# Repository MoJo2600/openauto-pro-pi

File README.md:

# Automotive power hat for OpenAuto

This hat is designed to work together with OpenAuto Pro and deliver some functionality which makes integrating OpenAuto into your car easier.

## Work in progress - a word of warning

I'm not an electronics professional and this board is currently work in progress. If somebody is willing to do a indepth review with me I would be very glad. Reach out to me on twitter [@MoJo2600](https://twitter.com/MoJo2600).

## Features

* Integrated 5A Power Supply
* Wide range power input (+7.5V to +40V)
* On-/Off circuit with ignition sensing
* 2 Digital inputs for e.g. reverse signal
* I2S sound
* RTC clock
* CSI to HDMI adapters to connect a display and camera
  * I2C bus availabe on the display connector for a light sensor
* Designed to fit exactly onto a [Geekworm x825](https://wiki.geekworm.com/index.php/X825) SSD V1 (Not tested with V2 but should fit)

## Connections
the following pins are used on the pi.

|Connection     | Pin |
|---------------|-----|
|I2C            |BCM23|
|I2C            |BCM24|
|REVERSE        |BCM8 |
|LIGHT          |BCM25|
|PI UP          |BCM23|
|SHUTDOWN       |BCM24|
|I2S DAC MUTE   |BCM16|
|I2S DAC BITCLK |BCM18|
|I2S DAC LRCLK  |BCM19|
|I2S DAC DATAIN |BCM21|

## OpenAuto Pro Setup

Set up the device before you add the header to the raspberry pi. The device will constantly reboot if the Start / Stop script is not installed. An alternative is to bridge the 3.3V pin from the raspberry pi to BCM23.

### Start / Stop script

Copy `scripts/startstop.sh` to the openauto device.

`sudo bash startstop.sh`

### I2C Real Time Clock

Make sure the battery has contact to the pad on the minus size. Mine had not and I added a little bit of solder to the pad to make contact.

```
# select pcf85063
```

### Rearview camera script

This script will open raspivid and show the picture of the rear camera.

Copy all files to the raspberry pi and start the setup

`./setup.sh`

### Brightness control script

My brightness script utilizes the TSL2561 ambient light sensor. The script implements a recommendation from analog devices
https://www.analog.com/en/design-notes/a-simple-implementation-of-lcd-brightness-control-using-the-max44009-ambientlight-sensor.html

Copy all files to the raspberry pi and start the setup

`./setup.sh`

### Audio output

The current audio circuit is not really usable. The output is very noisy und the signal is too low to usw it effectively. If you want to try i t you can use the following settings.

Add the overlays to `/boot/config.txt`

```
dtoverlay=hifiberry-dac
dtoverlay=i2s-mmap
```

After a reboot the sound should be working. Expect a line level output. If the volume is set to high, there will be clipping.

## Fixes for Issues

### Bluetooth Dongle BCM20702A1 not working

I had to install the bluetooth firmware for my broadcom bluetooth dongle from this repository https://github.com/winterheart/broadcom-bt-firmware.

The error in dmesg was:

```
bluetooth hci1: Direct firmware load for brcm/BCM20702A1-0a5c-21e8 failed with error -2
Bluetooth: hci1: BCM: Patch brcm/BCM20702A1-0a5c-21e8 not found
```

The installation was easy:

```
wget https://github.com/winterheart/broadcom-bt-firmware/raw/master/brcm/BCM20702A1-0a5c-21e8.hcd
sudo cp *.hcd /lib/firmware/brcm/
```

## History

Here is a picture of prototype V1 with a Mouseberry power supply.

## Disclaimer

Due to the fact we are not providing a product in the legal sense, we are also not providing any warranty in any aspect.

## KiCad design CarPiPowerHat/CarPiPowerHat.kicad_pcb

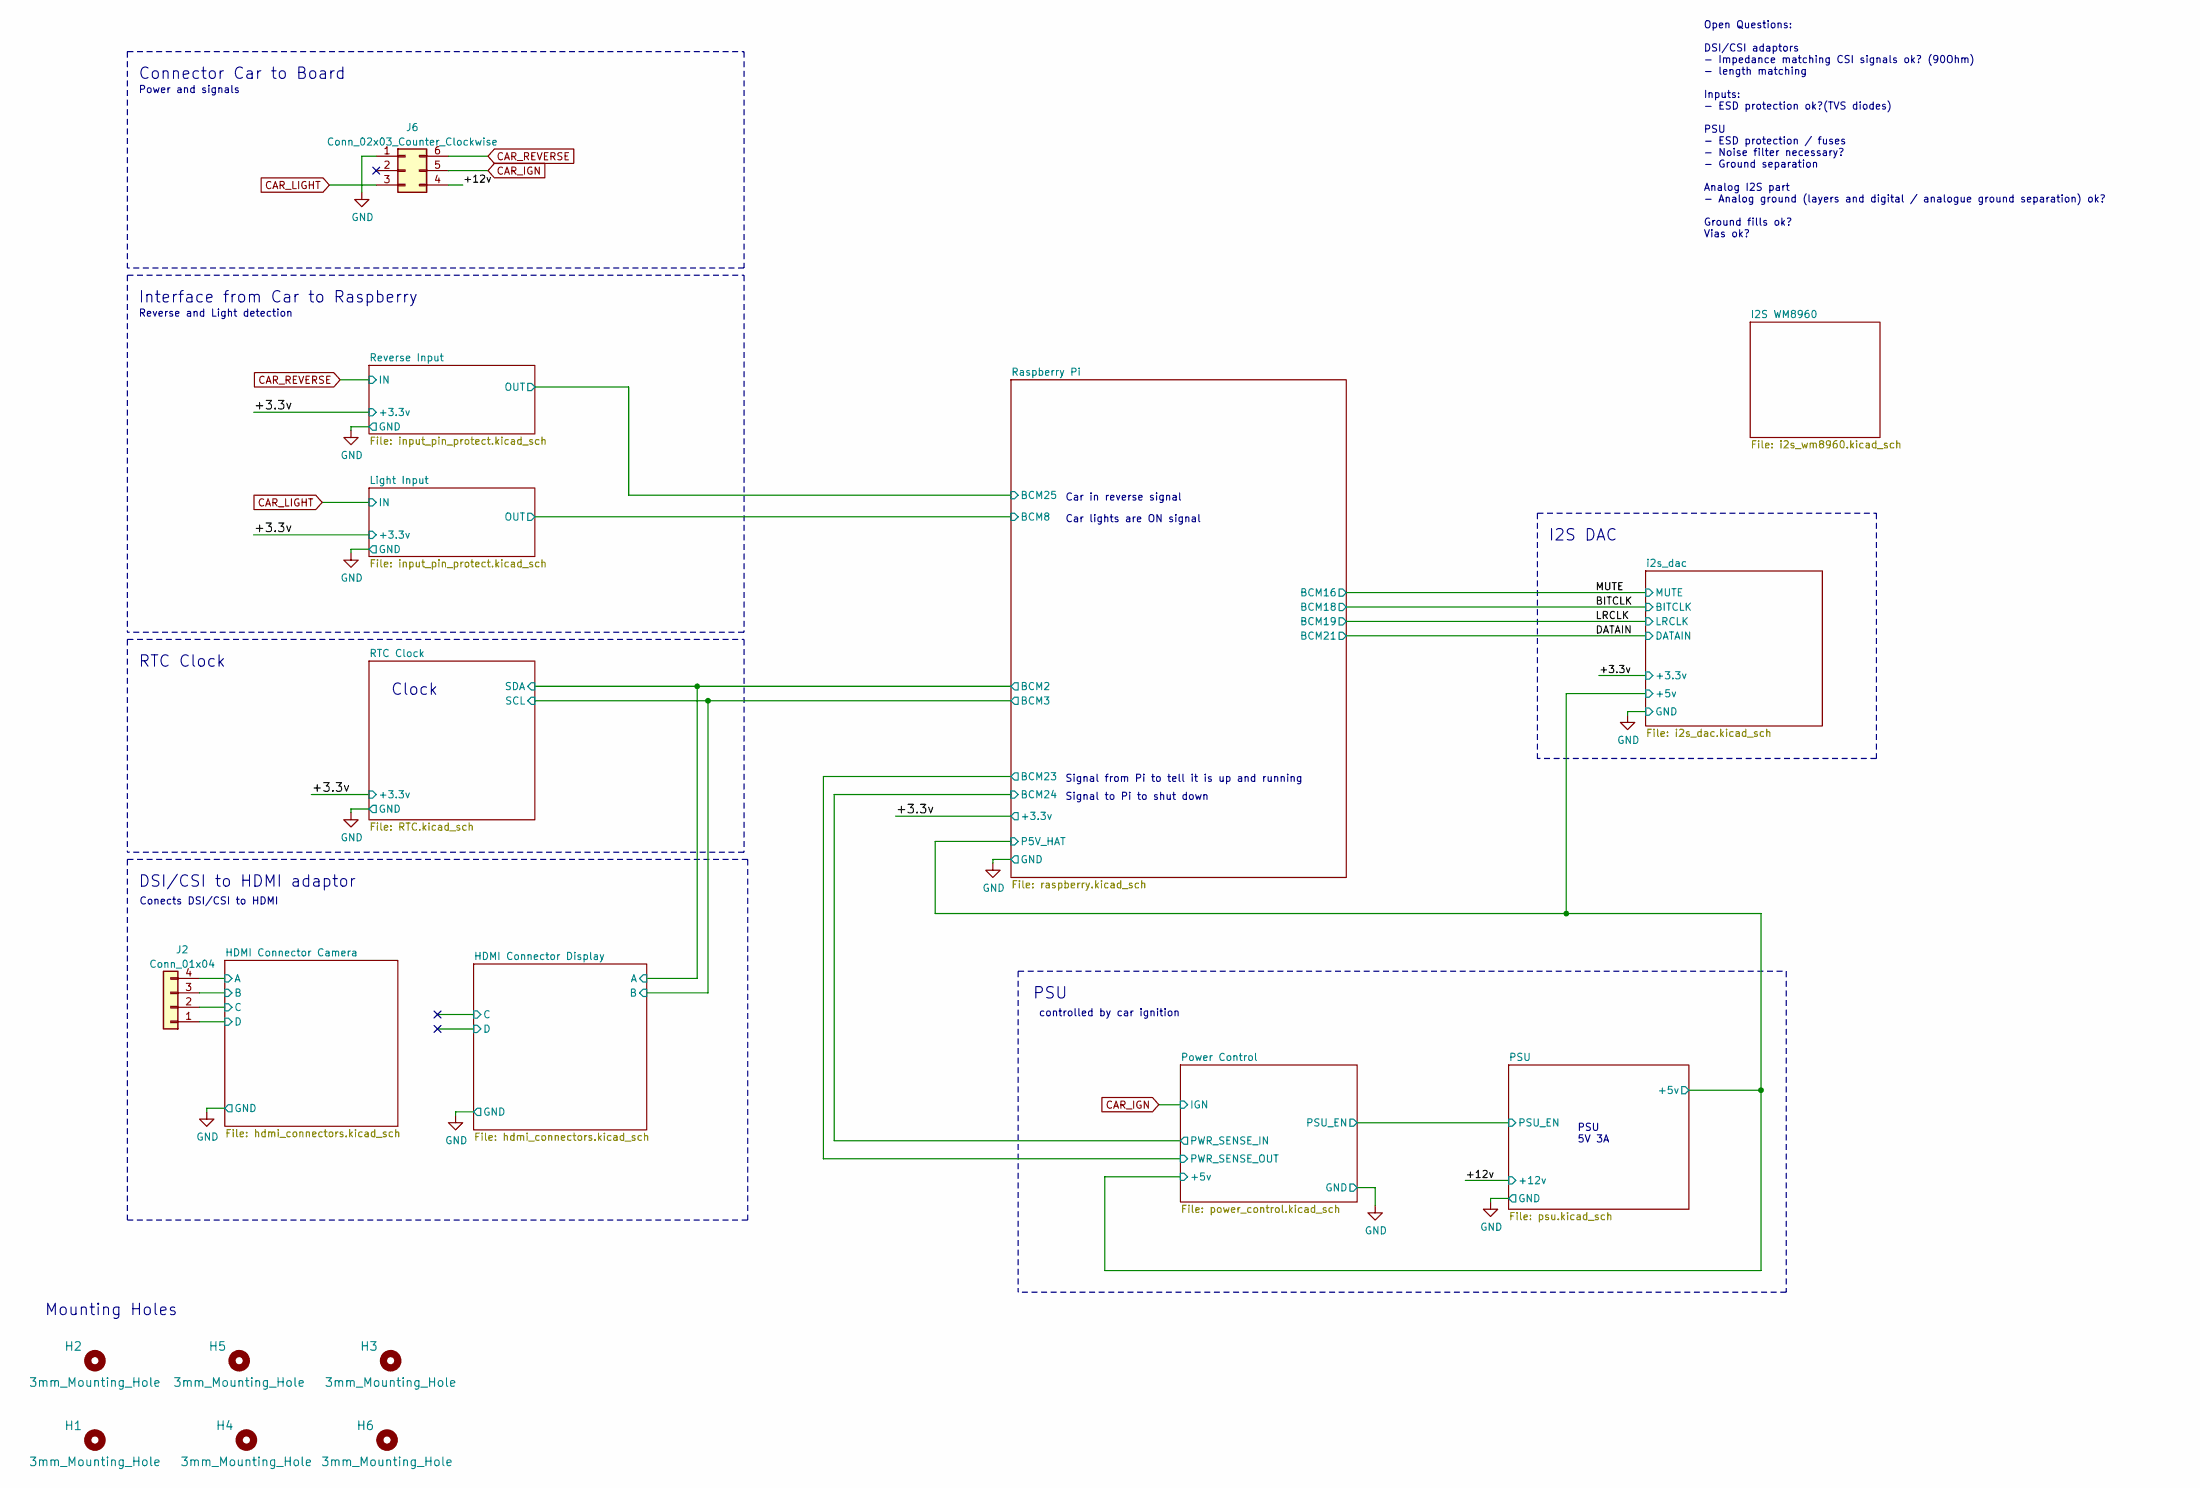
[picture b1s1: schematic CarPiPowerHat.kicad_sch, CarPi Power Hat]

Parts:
H1, H2, H3, H4, H5, H6: 3mm_Mounting_Hole; MountingHole_2.7mm_M2.5
J2: Conn_01x04; PinHeader_1x04_P2.00mm_Vertical
J6: Conn_02x03_Counter_Clockwise; Molex_Mini-Fit_Jr_5569-06A2_2x03_P4.20mm_Horizontal; MouserNr 538-50-36-1798

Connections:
/+12v: J6.4; also elsewhere on the board
/HDMI Connector Camera/A: J2.4; also elsewhere on the board
/HDMI Connector Camera/B: J2.3; also elsewhere on the board
/HDMI Connector Camera/C: J2.2; also elsewhere on the board
/HDMI Connector Camera/D: J2.1; also elsewhere on the board
CAR_IGN: J6.5; also elsewhere on the board
CAR_LIGHT: J6.3; also elsewhere on the board
CAR_REVERSE: J6.6; also elsewhere on the board
GND: J6.1; also elsewhere on the board

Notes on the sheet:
Open Questions: DSI/CSI adaptors - Impedance matching CSI signals ok? (90Ohm) - length matching Inputs: - ESD protection ok?(TVS diodes) PSU - ESD protection / fuses - Noise filter necessary? - Ground separation Analog I2S part - Analog ground (layers and digital / analogue ground separation) ok? G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
PSU 5V 3A
Mounting Holes
Power and signals
PSU
I2S DAC
RTC Clock
controlled by car ignition
Clock
Signal to Pi to shut down
Signal from Pi to tell it is up and running
Car lights are ON signal
Connector Car to Board
DSI/CSI to HDMI adaptor
Reverse and Light detection
Conects DSI/CSI to HDMI
Car in reverse signal
Interface from Car to Raspberry

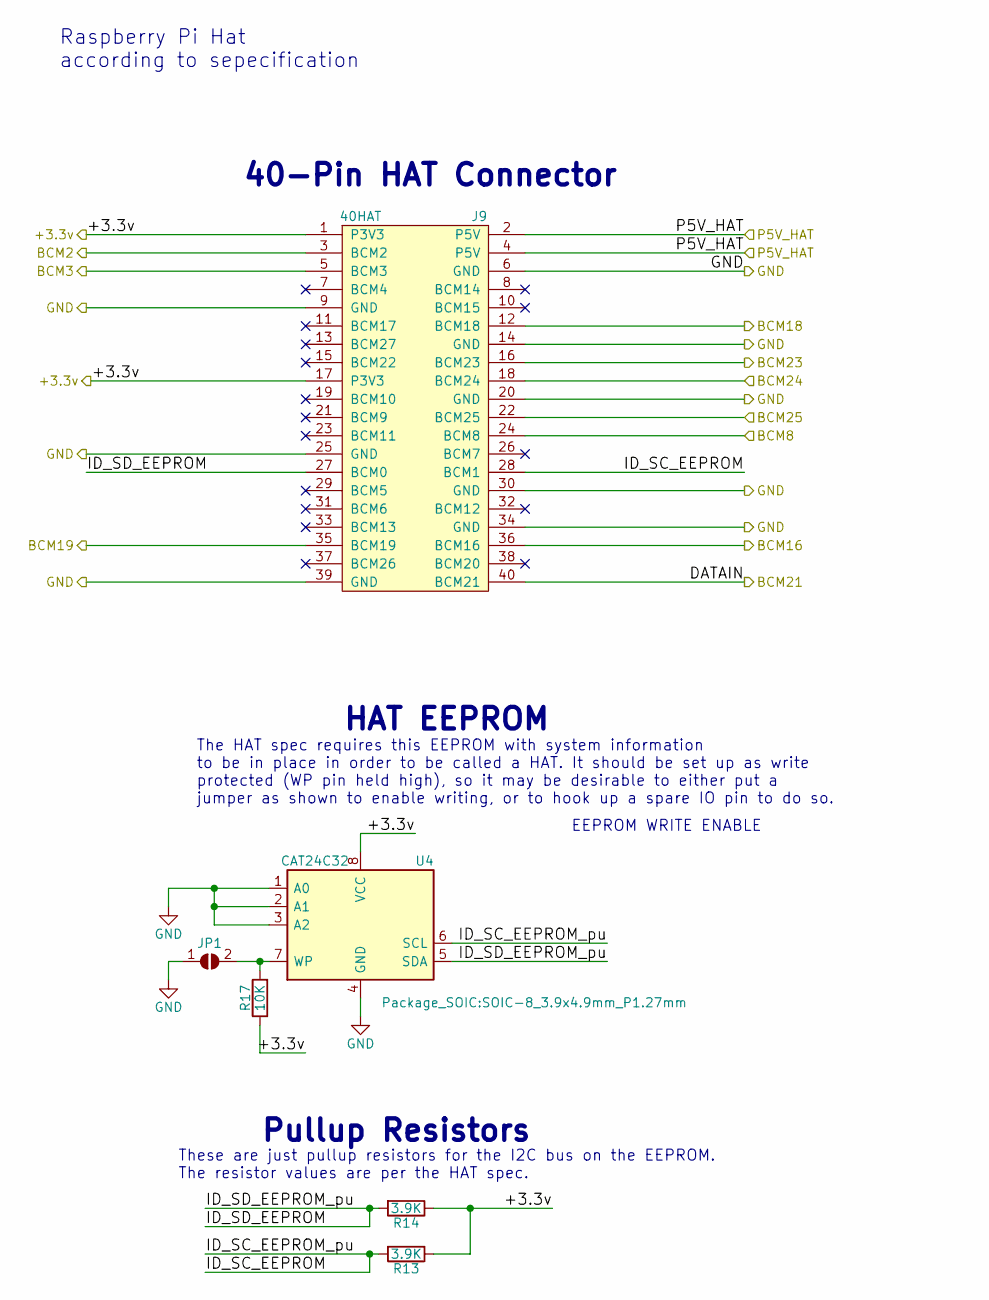
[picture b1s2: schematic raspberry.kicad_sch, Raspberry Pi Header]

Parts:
J9: 40HAT; PinSocket_2x20_P2.54mm_Vertical
JP1: SolderJumper_2_Open; SolderJumper-2_P1.3mm_Open_RoundedPad1.0x1.5mm
R13, R14: 3.9K; R_0603_1608Metric; LCSC C23018
R17: 10K; R_0603_1608Metric; LCSC C25804
U4: CAT24C32; SOIC-8_3.9x4.9mm_P1.27mm; LCSC C81193

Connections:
/+3.3v: J9.1 (P3V3), J9.17 (P3V3), R13.1, R14.1, R17.1, U4.8 (VCC); also elsewhere on the board
/BITCLK: J9.12 (BCM18); also elsewhere on the board
/DATAIN: J9.40 (BCM21); also elsewhere on the board
/LRCLK: J9.35 (BCM19); also elsewhere on the board
/Light Input/OUT: J9.24 (BCM8); also elsewhere on the board
/MUTE: J9.36 (BCM16); also elsewhere on the board
/Power Control/PWR_SENSE_IN: J9.18 (BCM24); also elsewhere on the board
/RTC Clock/SCL: J9.5 (BCM3); also elsewhere on the board
/RTC Clock/SDA: J9.3 (BCM2); also elsewhere on the board
/Raspberry Pi/BCM25: J9.22 (BCM25); also elsewhere on the board
/Raspberry Pi/ID_SC_EEPROM: J9.28 (BCM1), R13.2, U4.6 (SCL)
/Raspberry Pi/ID_SD_EEPROM: J9.27 (BCM0), R14.2, U4.5 (SDA)
/Raspberry Pi/P5V_HAT: J9.2 (P5V), J9.4 (P5V); also elsewhere on the board
GND: J9.6 (GND), J9.9 (GND), J9.14 (GND), J9.20 (GND), J9.25 (GND), J9.30 (GND), J9.34 (GND), J9.39 (GND), JP1.1 (A), U4.1 (A0), U4.2 (A1), U4.3 (A2), U4.4 (GND); also elsewhere on the board
unnamed: JP1.2 (B), R17.2, U4.7 (WP)
PWR_SENSE_OUT: J9.16 (BCM23); also elsewhere on the board

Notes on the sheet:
EEPROM WRITE ENABLE
Pullup Resistors
40-Pin HAT Connector
HAT EEPROM
The HAT spec requires this EEPROM with system information to be in place in order to be called a HAT. It should be set up as write protected (WP pin held high), so it may be desirable to either put a jumper as shown to enable writing, or to hook up a spare IO pin to do so.
Raspberry Pi Hat according to sepecification
These are just pullup resistors for the I2C bus on the EEPROM. The resistor values are per the HAT spec.

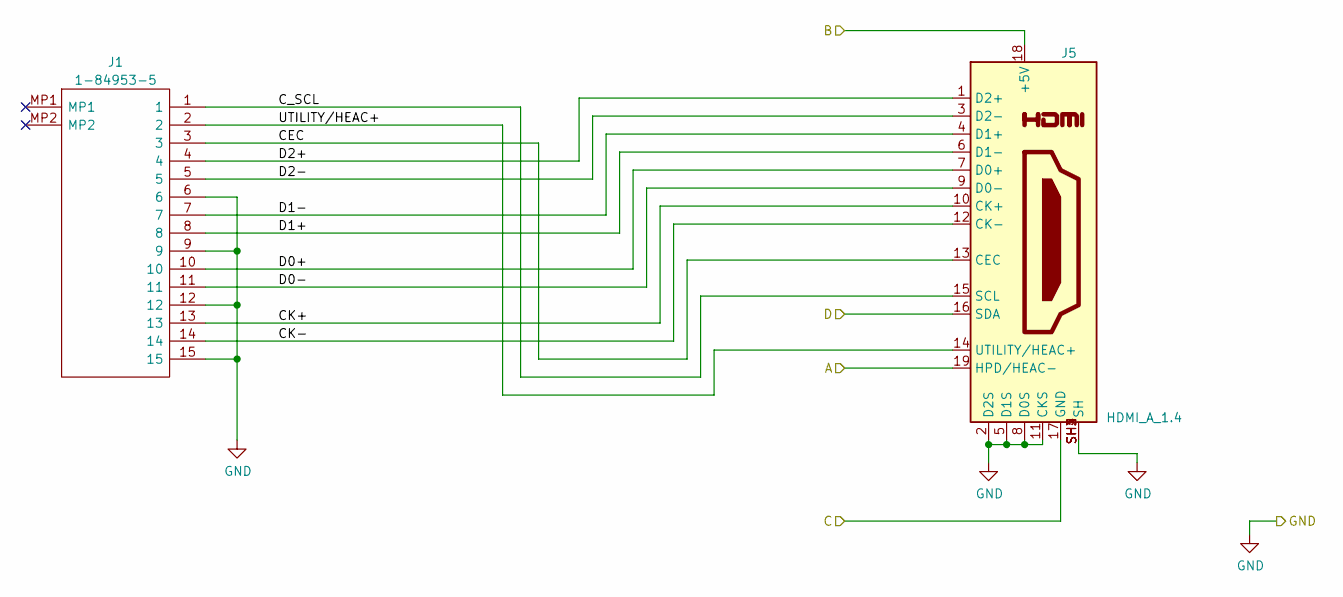
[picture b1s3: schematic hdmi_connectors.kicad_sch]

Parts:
J1: 1-84953-5; 1849535; Manufacturer_Part_Number 1-84953-5; Mouser Part Number 571-1-84953-5
J5: HDMI_A_1.4; EDAC 690-019-298-412; Part Description HDMI Connector, Right Angle, 19 Contact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

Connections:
/HDMI Connector Display/C: J5.17 (GND)
/HDMI Connector Display/CEC: J1.3, J5.13 (CEC)
/HDMI Connector Display/CK+: J1.13, J5.10 (CK+)
/HDMI Connector Display/CK-: J1.14, J5.12 (CK-)
/HDMI Connector Display/C_SCL: J1.1, J5.15 (SCL)
/HDMI Connector Display/D: J5.16 (SDA)
/HDMI Connector Display/D0+: J1.10, J5.7 (D0+)
/HDMI Connector Display/D0-: J1.11, J5.9 (D0-)
/HDMI Connector Display/D1+: J1.8, J5.6 (D1-)
/HDMI Connector Display/D1-: J1.7, J5.4 (D1+)
/HDMI Connector Display/D2+: J1.4, J5.1 (D2+)
/HDMI Connector Display/D2-: J1.5, J5.3 (D2-)
/HDMI Connector Display/UTILITY/HEAC+: J1.2, J5.14 (UTILITY/HEAC+)
/RTC Clock/SCL: J5.18 (+5V); also elsewhere on the board
/RTC Clock/SDA: J5.19 (HPD/HEAC-); also elsewhere on the board
GND: J1.6, J1.9, J1.12, J1.15, J5.2 (D2S), J5.5 (D1S), J5.8 (D0S), J5.11 (CKS), J5.SH1 (SH), J5.SH2 (SH), J5.SH3 (SH), J5.SH4 (SH); also elsewhere on the board

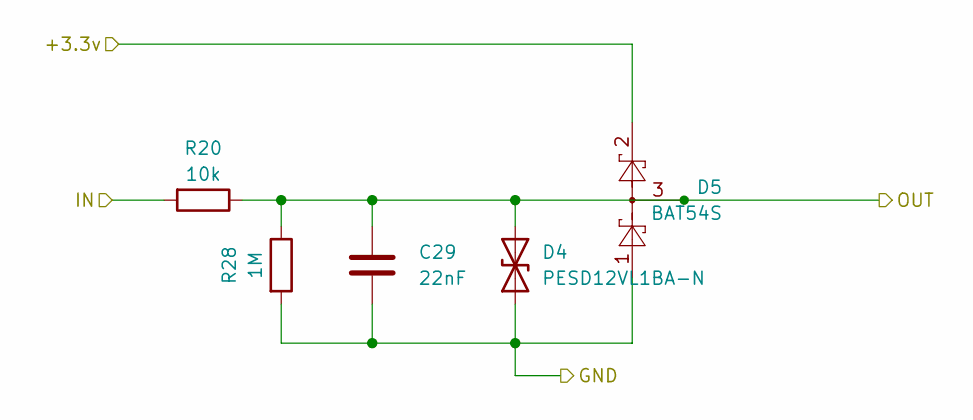
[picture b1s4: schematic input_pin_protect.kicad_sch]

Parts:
C29: 22nF; C_0805_2012Metric; LCSC C1729
D4: PESD12VL1BA-N; D_SOD-323; LCSC C314261
D5: BAT54S; SOT-23; LCSC C408389
R20: 10k; R_0805_2012Metric_Pad1.20x1.40mm_HandSolder; LCSC C17414
R28: 1M; R_0805_2012Metric_Pad1.20x1.40mm_HandSolder; LCSC C17514

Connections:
/+3.3v: D5.2; also elsewhere on the board
/Raspberry Pi/BCM25: C29.1, D4.2 (A2), D5.3, R20.1, R28.1; also elsewhere on the board
CAR_REVERSE: R20.2; also elsewhere on the board
GND: C29.2, D4.1 (A1), D5.1, R28.2; also elsewhere on the board

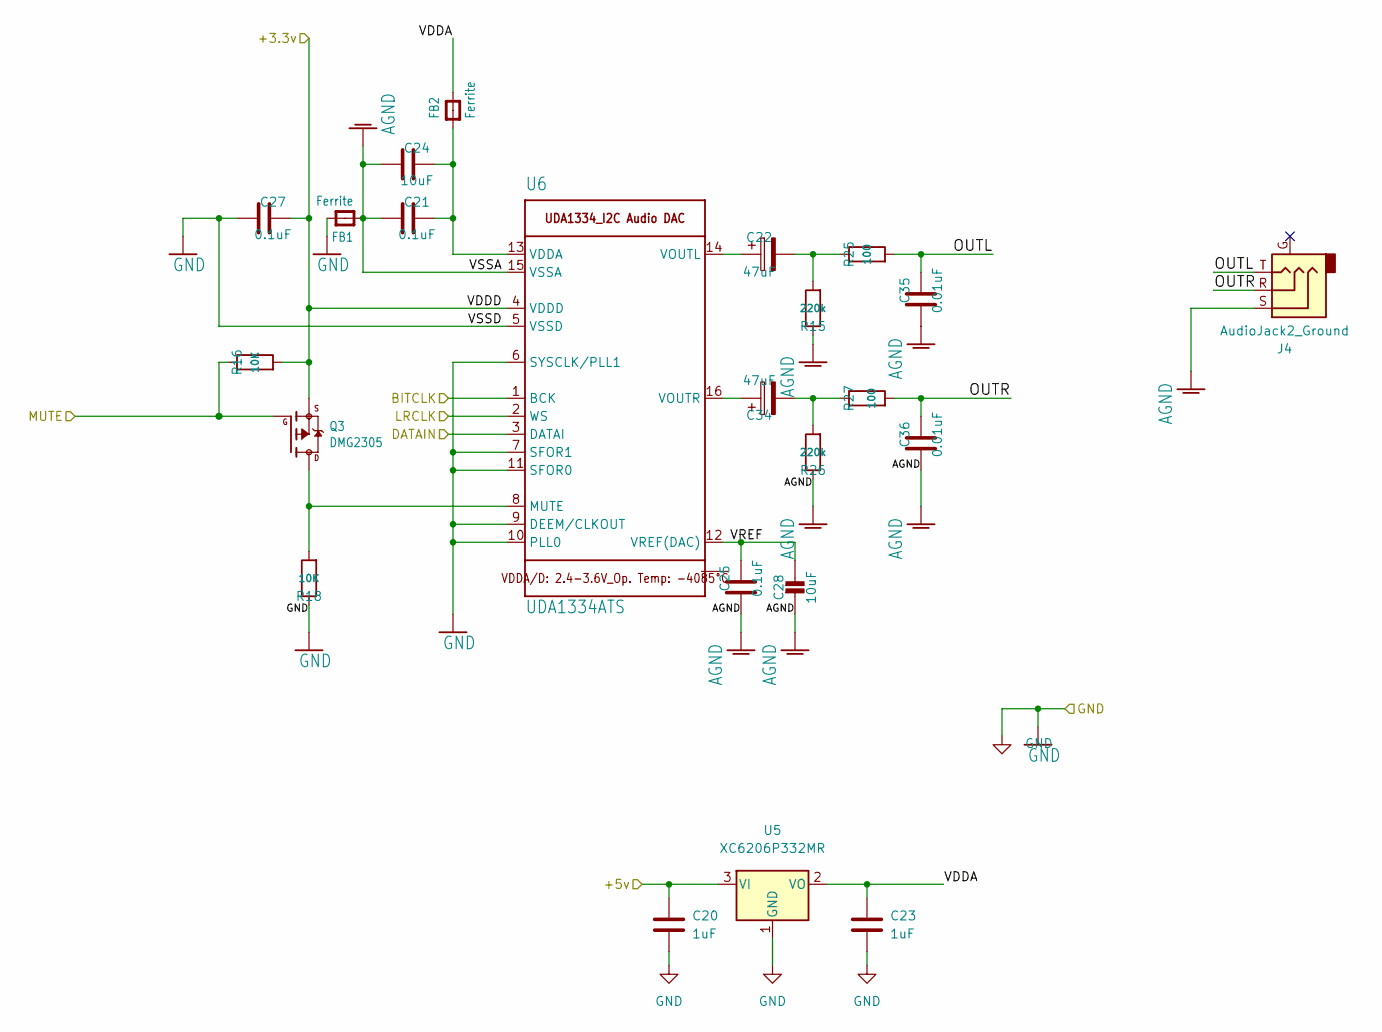
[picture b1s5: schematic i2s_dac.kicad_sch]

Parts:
C20, C23: 1uF; C_0805_2012Metric_Pad1.18x1.45mm_HandSolder; LCSC C28323
C21, C25, C27: 0.1uF; C_0603_1608Metric; LCSC C14663
C22, C34: 47uF; CP_Elec_6.3x7.7; LCSC C164078
C24, C28: 10uF; C_0805_2012Metric; LCSC C15850
C35, C36: 0.01uF; C_0603_1608Metric; LCSC C57112
FB1, FB2: Ferrite; R_0805_2012Metric; LCSC C1017
J4: AudioJack2_Ground; Jack_3.5mm_CUI_SJ-3524-SMT_Horizontal; Mouser 490-SJ3524-SMT-TR-GR
Q3: DMG2305; SOT-23; LCSC C144153
R15, R26: 220k; R_0805_2012Metric; LCSC C17521
R16, R18: 10K; R_0603_1608Metric; LCSC C25804
R25, R27: 100; R_0603_1608Metric; LCSC C22775
U5: XC6206P332MR; SOT-23; LCSC C5446
U6: UDA1334ATS; SSOP-16_4.4x5.2mm_P0.65mm; LCSC C494494

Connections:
/+3.3v: C27.1, Q3.2 (S), R16.2, U6.4 (VDDD); also elsewhere on the board
/BITCLK: U6.1 (BCK); also elsewhere on the board
/DATAIN: U6.3 (DATAI); also elsewhere on the board
/LRCLK: U6.2 (WS); also elsewhere on the board
/MUTE: Q3.1 (G), R16.1; also elsewhere on the board
/Raspberry Pi/P5V_HAT: C20.1, U5.3 (VI); also elsewhere on the board
/i2s_dac/OUTL: C35.1, J4.T, R25.2
/i2s_dac/OUTR: C36.1, J4.R, R27.2
/i2s_dac/VDDA: C23.1, FB2.2, U5.2 (VO)
/i2s_dac/VREF: C25.1, C28.1, U6.12 (VREF(DAC))
AGND: C21.2, C24.2, C25.2, C28.2, C35.2, C36.2, FB1.1, J4.S, R15.1, R26.1, U6.15 (VSSA)
GND: C20.2, C23.2, C27.2, FB1.2, R18.1, U5.1 (GND), U6.5 (VSSD), U6.6 (SYSCLK/PLL1), U6.7 (SFOR1), U6.9 (DEEM/CLKOUT), U6.10 (PLL0), U6.11 (SFOR0); also elsewhere on the board
unnamed: C21.1, C24.1, FB2.1, U6.13 (VDDA)
unnamed: C22.1, U6.14 (VOUTL)
unnamed: C22.2, R15.2, R25.1
unnamed: C34.1, U6.16 (VOUTR)
unnamed: C34.2, R26.2, R27.1
unnamed: Q3.3 (D), R18.2, U6.8 (MUTE)

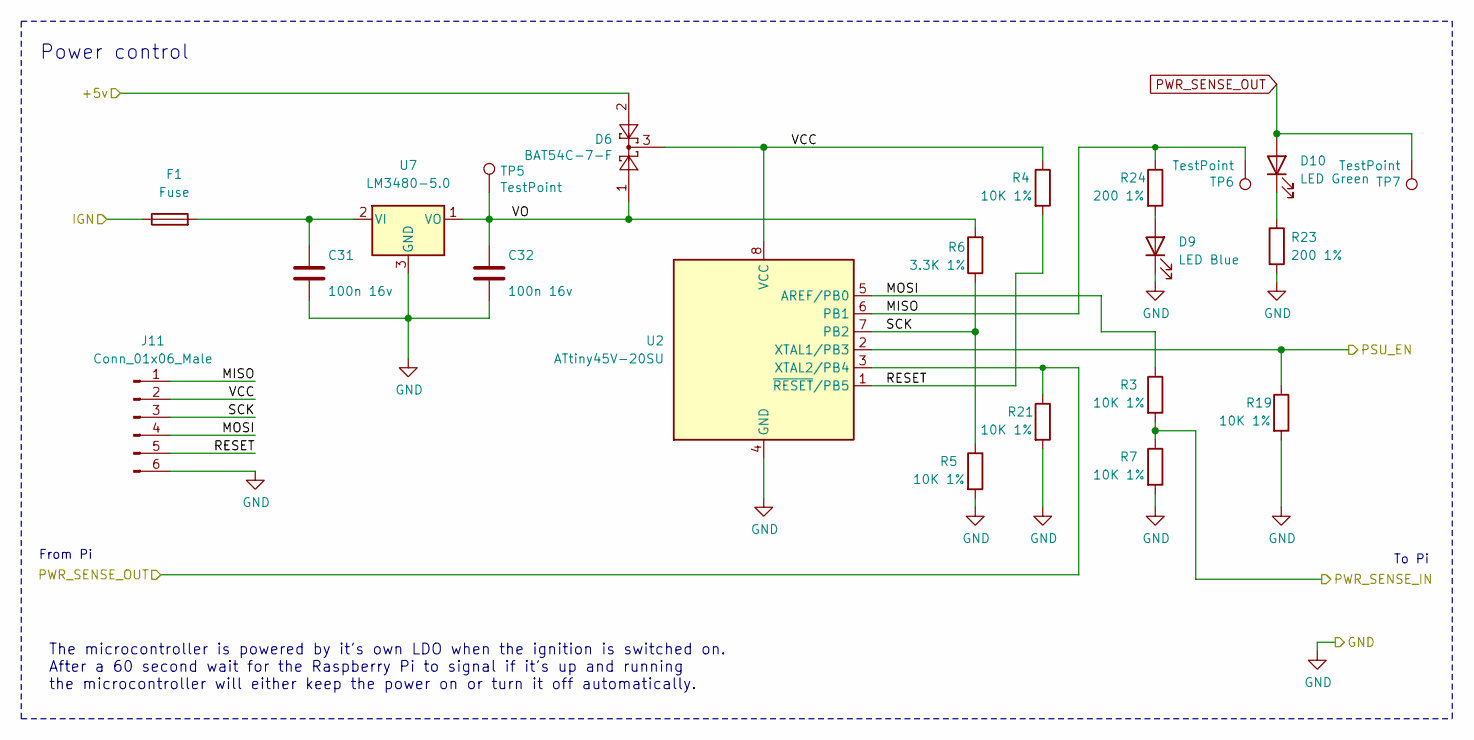
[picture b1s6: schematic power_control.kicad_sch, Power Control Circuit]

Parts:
C31, C32: 100n 16v; C_0402_1005Metric; Part Description 0.1uF 10% 16V Ceramic Capacitor X7R 040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; LCSC C1525
D6: BAT54C-7-F; SOT-23; Part Description Diode Array 1 Pair Common Cathode Schot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; LCSC C37704
D9: LED Blue; LED_0603_1608Metric; LCSC C72041
D10: LED Green; LED_0603_1608Metric; LCSC C72043
F1: Fuse; Fuse_1206_3216Metric_Pad1.42x1.75mm_HandSolder; LCSC C206984
J11: Conn_01x06_Male; PinHeader_2x03_P2.54mm_Vertical
R3, R4, R5, R7, R19, R21: 10K 1%; R_0603_1608Metric; Part Description Resistor 12K M1005 1% 63mW; LCSC C25804
R6: 3.3K 1%; R_0603_1608Metric; Part Description Resistor 12K M1005 1% 63mW; LCSC C22978
R23: 200 1%; R_0402_1005Metric; LCSC C25087
R24: 200 1%; R_0402_1005Metric; Part Description Resistor 12K M1005 1% 63mW; LCSC C25087
TP5, TP6, TP7: TestPoint; TestPoint_Pad_D1.0mm
U2: ATtiny45V-20SU; SOIC-8W_5.3x5.3mm_P1.27mm; LCSC C62689
U7: LM3480-5.0; SOT-23; LCSC C129960

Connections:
/PSU/PSU_EN: R19.1, U2.2 (XTAL1/PB3); also elsewhere on the board
/Power Control/MISO: J11.1, R24.1, TP6.1, U2.6 (PB1)
/Power Control/MOSI: J11.4, R3.1, U2.5 (AREF/PB0)
/Power Control/PWR_SENSE_IN: R3.2, R7.1; also elsewhere on the board
/Power Control/RESET: J11.5, R4.2, U2.1 (~RESET/PB5)
/Power Control/SCK: J11.3, R5.1, R6.1, U2.7 (PB2)
/Power Control/VCC: D6.3, J11.2, R4.1, U2.8 (VCC)
/Power Control/VO: C32.1, D6.1, R6.2, TP5.1, U7.1 (VO)
/Raspberry Pi/P5V_HAT: D6.2; also elsewhere on the board
CAR_IGN: F1.1; also elsewhere on the board
GND: C31.2, C32.2, D9.1 (K), J11.6, R5.2, R7.2, R19.2, R21.2, R23.2, U2.4 (GND), U7.3 (GND); also elsewhere on the board
unnamed: C31.1, F1.2, U7.2 (VI)
unnamed: D9.2 (A), R24.2
unnamed: D10.1 (K), R23.1
PWR_SENSE_OUT: D10.2 (A), R21.1, TP7.1, U2.3 (XTAL2/PB4); also elsewhere on the board

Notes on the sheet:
Power control
The microcontroller is powered by it's own LDO when the ignition is switched on. After a 60 second wait for the Raspberry Pi to signal if it's up and running the microcontroller will either keep the power on or turn it off automatically.
From Pi
To Pi

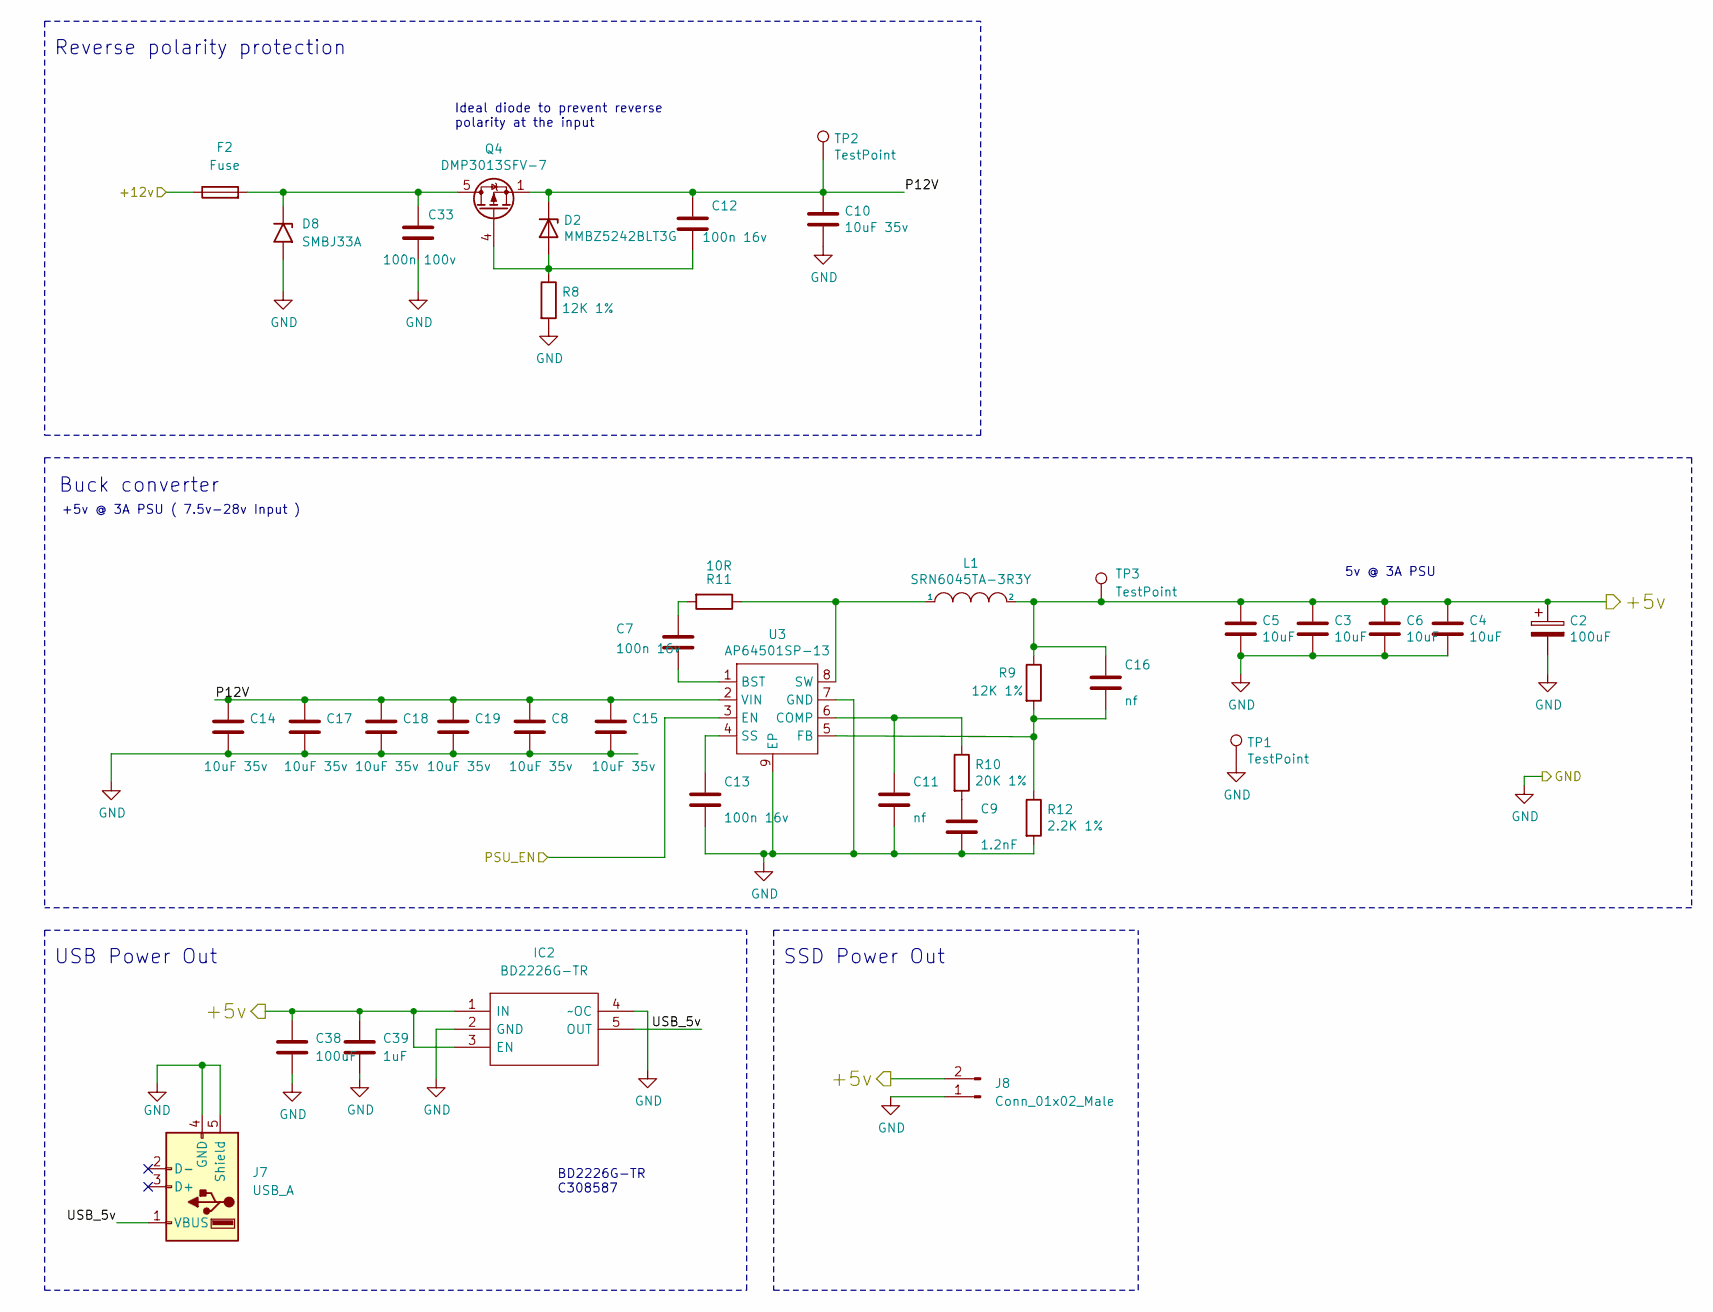
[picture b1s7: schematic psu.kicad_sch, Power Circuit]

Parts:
C2: 100uF; CP_EIA-7343-31_Kemet-D; Part Description Capacitor, SP-Cap, 100u, 6.3V, 15mR ESR
C3, C4, C5, C6: 10uF; C_0805_2012Metric; Part Description 10uF 10% 10V Ceramic Capacitor X7R 0805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; LCSC C15850
C7, C12, C13: 100n 16v; C_0402_1005Metric; Part Description 0.1uF 10% 16V Ceramic Capacitor X7R 040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; LCSC C1525
C8, C10, C14, C15, C17, C18, C19: 10uF 35v; C_0805_2012Metric; Part Description 10uF 10% or 20% 35V Ceramic Capacitor X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; LCSC C440198
C9: 1.2nF; C_0603_1608Metric; Part Description 1200pF 10% 10V Ceramic Capacitor X5R 04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; LCSC C30615
C11: nf; C_0402_1005Metric
C16: nf; C_0402_1005Metric; Part Description 220 pF, 50 V, 0402 [1005 Metric], ± 5%,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
C33: 100n 100v; C_0805_2012Metric; Part Description 0.1uF 10% 100V Ceramic Capacitor X5R 04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; LCSC C28233
C38: 100uF; C_1206_3216Metric_Pad1.33x1.80mm_HandSolder; LCSC C15008
C39: 1uF; C_0603_1608Metric_Pad1.08x0.95mm_HandSolder; LCSC C15849
D2: MMBZ5242BLT3G; D_SOT-23_ANK; Part Description Zener Diode 12V 225mW 5% Surface Mount 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; LCSC C268585
D8: SMBJ33A; D_SMB; LCSC C353366
F2: Fuse; Fuse_Littelfuse-NANO2-451_453
IC2: BD2226G-TR; SOT95P280X125-5N; Manufacturer_Part_Number BD2226G-TR; Mouser Part Number 755-BD2226G-TR
J7: USB_A; USB_A_Wuerth_614004134726_Horizontal; Mouser No 710-614004134726
J8: Conn_01x02_Male; JST_XH_S2B-XH-A_1x02_P2.50mm_Horizontal
L1: SRN6045TA-3R3Y; L_Bourns_SRN6045TA; Part Description 3.3µH Semi-Shielded Wirewound Inductor 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
Q4: DMP3013SFV-7; Diodes_PowerDI3333-8; Part Description DMP3013SFV-7 - Power MOSFET, P Channel,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; LCSC C264098
R8, R9: 12K 1%; R_0402_1005Metric; Part Description Resistor 12K M1005 1% 63mW; LCSC C25752
R10: 20K 1%; R_0402_1005Metric; Part Description Resistor 20K M1005 1% 63mW; LCSC C25765
R11: 10R; R_0402_1005Metric; Part Description Resistor 10R M1005 1% 63mW; LCSC C25077
R12: 2.2K 1%; R_0402_1005Metric; Part Description Resistor 2.2K M1005 1% 63mW; LCSC C25879
TP1, TP2, TP3: TestPoint; TestPoint_Pad_D1.0mm
U3: AP64501SP-13; SOIC-8-1EP_3.9x4.9mm_P1.27mm_EP2.95x4.9mm_Mask2.71x3.4mm_Th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; Part Description Buck Switching Regulator IC Positive Ad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; LCSC C2071517

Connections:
/+12v: F2.1; also elsewhere on the board
/PSU/P12V: C8.1, C10.1, C12.1, C14.1, C15.1, C17.1, C18.1, C19.1, D2.1 (K), Q4.1 (S), Q4.2 (S), Q4.3 (S), TP2.1, U3.2 (VIN)
/PSU/PSU_EN: U3.3 (EN); also elsewhere on the board
/PSU/USB_5v: IC2.5 (OUT), J7.1 (VBUS)
/Raspberry Pi/P5V_HAT: C2.1, C3.1, C4.1, C5.1, C6.1, C16.1, C38.1, C39.1, IC2.1 (IN), IC2.3 (EN), J8.2, L1.2, R9.1, TP3.1; also elsewhere on the board
GND: C2.2, C3.2, C4.2, C5.2, C6.2, C8.2, C9.2, C10.2, C11.2, C13.2, C14.2, C15.2, C17.2, C18.2, C19.2, C33.2, C38.2, C39.2, D8.2 (A2), IC2.2 (GND), IC2.4 (~OC), J7.4 (GND), J7.5 (Shield), J8.1, R8.2, R12.2, TP1.1, U3.7 (GND), U3.9 (EP); also elsewhere on the board
unnamed: C7.1, R11.2
unnamed: C7.2, U3.1 (BST)
unnamed: C9.1, R10.2
unnamed: C11.1, R10.1, U3.6 (COMP)
unnamed: C12.2, D2.2 (A), Q4.4 (G), R8.1
unnamed: C13.1, U3.4 (SS)
unnamed: C16.2, R9.2, R12.1, U3.5 (FB)
unnamed: C33.1, D8.1 (A1), F2.2, Q4.5 (D)
unnamed: L1.1, R11.1, U3.8 (SW)

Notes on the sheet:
BD2226G-TR C308587
SSD Power Out
USB Power Out
+5v @ 3A PSU ( 7.5v-28v Input )
Reverse polarity protection
Ideal diode to prevent reverse polarity at the input
5v @ 3A PSU
Buck converter

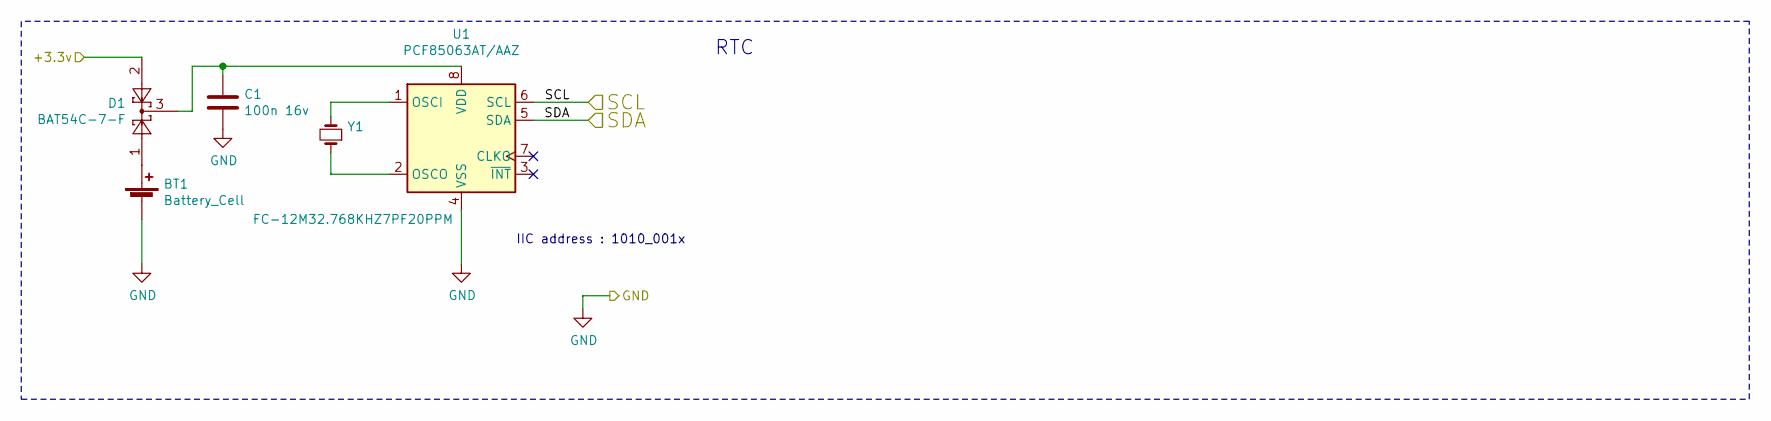
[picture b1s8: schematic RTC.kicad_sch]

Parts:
BT1: Battery_Cell; BatteryHolder_Keystone_3034_1x20mm; Part Description Battery Retainer Coin, 20.0mm 1 Cell SM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; Mouser No 534-3034
C1: 100n 16v; C_0402_1005Metric; Part Description 0.1uF 10% 16V Ceramic Capacitor X7R 040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; LCSC C1525
D1: BAT54C-7-F; SOT-23; Part Description Diode Array 1 Pair Common Cathode Schot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; LCSC C37704
U1: PCF85063AT/AAZ; SOIC-8_3.9x4.9mm_P1.27mm; Part Description Real Time Clock (RTC) IC Clock/Calendar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; LCSC C7440
Y1: FC-12M32.768KHZ7PF20PPM; Crystal_SMD_3215-2Pin_3.2x1.5mm; Part Description Crystal 32.768KHz 7pF 20pmm; LCSC C99009

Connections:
/+3.3v: D1.2; also elsewhere on the board
/RTC Clock/SCL: U1.6 (SCL); also elsewhere on the board
/RTC Clock/SDA: U1.5 (SDA); also elsewhere on the board
GND: BT1.2 (-), C1.2, U1.4 (VSS); also elsewhere on the board
unnamed: BT1.1 (+), D1.1
unnamed: C1.1, D1.3, U1.8 (VDD)
unnamed: U1.1 (OSCI), Y1.2
unnamed: U1.2 (OSCO), Y1.1

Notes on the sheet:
RTC
IIC address : 1010_001x
